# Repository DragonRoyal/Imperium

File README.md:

# Imperium
### An Autonomous, Sensor-Driven Chessboard with Electromagnetic Piece Control

## Abstract

**Imperium** is a fully autonomous chessboard that detects and moves pieces using a precision electromagnetic gantry, per-square Hall-effect sensing, and CNC-style motion control. The system integrates custom mechanical design, multi-PCB electronics, and firmware-level motion planning to deliver seamless, repeatable gameplay without manual calibration.

---

## System Overview

```mermaid
flowchart LR
    Pieces[Chess Pieces — Magnets]
    Sensors[Hall Sensor Matrix — 64 Squares]
    Mux[16:1 Multiplexers]
    MCU[ESP32 Master Controller]
    Drivers[TMC2209 Motor Drivers]
    Motors[Stepper Motors — T-Bot Gantry]
    Magnet[Electromagnet]

    Pieces --> Sensors
    Sensors --> Mux
    Mux --> MCU
    MCU --> Drivers
    Drivers --> Motors
    MCU --> Magnet
```

## Project Media

### Completed System

<p align="center">
  <em>Figure 2: Fully assembled Imperium chessboard</em>
</p>

### Videos
- 🎥 [demonstration video](https://www.youtube.com/watch?v=dJfiPbZPBKA)
- 🎥 [piece movement](https://www.youtube.com/watch?v=BL-nZTy-D_8)

---

## Hardware Architecture

### Mechanical Subsystem

<p align="center">
  <em>CAD Figure: T-Bot gantry layout and belt routing</em>
</p>

**Gantry Design**
- Type: **T-Bot (CoreXY derivative)**
- Motors: 2× NEMA 17
- Linear motion: 2× MGN12 rails (450 mm)
- Drive: GT2 belts & pulleys
- End effector: Electromagnet (custom mount)

**Design Rationale**
- Compact footprint compared to CoreXY  
- Sufficient precision for chess (no micron-level requirement)  
- Reduced part count and cost  

---

## Sensing Architecture

### Hall Sensor Matrix
```mermaid
flowchart LR
    Square1[Square 1]
    Square2[Square 2]
    SquareN[Square 64]
    Mux1[16:1 MUX]
    MCU[ESP32]

    Square1 --> Mux1
    Square2 --> Mux1
    SquareN --> Mux1
    Mux1 --> MCU
```

<p align="center">
  <em>Figure 5: 64-square Hall-effect sensor grid</em>
</p>

- Sensors: **KTH-1601 (46 Gs threshold)**
- 1 sensor per square (64 total)
- Mounted beneath ~3 mm acrylic

**Why Hall Sensors**
- Instantaneous response  
- No ghosting (unlike reed switches)  
- Reliable removal detection  

---

### PCB Sheet Layout
```mermaid
flowchart TB
    PCB1[Hall PCB Sheet 1\n16 Sensors]
    PCB2[Hall PCB Sheet 2\n16 Sensors]
    PCB3[Hall PCB Sheet 3\n16 Sensors]
    PCB4[Hall PCB Sheet 4\n16 Sensors]
    Master[Master PCB]

    PCB1 --> Master
    PCB2 --> Master
    PCB3 --> Master
    PCB4 --> Master
```

<p align="center">
  <em>Figure 6: Hall sensor PCB sheet (100 mm × 400 mm)</em>
</p>

Each PCB sheet contains:
- 16 Hall sensors  
- 1× 16:1 multiplexer  
- Local decoupling capacitors  
- Ribbon cable interface  

Total sheets: **4**

---

## Control Electronics

### Master Control Board

<p align="center">
  <em>Figure 7: Master PCB functional block diagram</em>
</p>

**Core Components**
- MCU: **ESP32**
- Motor drivers: **2× TMC2209 (UART)**
- Power:
  - 12 V rail (motors + electromagnet)
  - Buck converter → 3.3 V logic
- Electromagnet switching via transistor

All schematics and footprints were custom-designed in KiCad.

---

### UART Motor Control
Chess pieces are moved exclusively along square edges rather than diagonals. This design choice:

Prevents collisions with stationary pieces

Simplifies motion planning

Ensures consistent and predictable movement paths

The gantry executes all moves as a sequence of orthogonal segments.

UART enables:
- Sensorless homing  
- Stall detection  
- Current tuning  
- Advanced diagnostics  

---

### Control Flow

1. **Board State Detection**  
   Hall sensor matrix scans current piece positions.

2. **Move Translation**  
   Chess moves converted into constrained paths.

3. **G-Code Generation**  
   Custom G-code enforces non-diagonal movement.

4. **Execution**  
   G-code executed by **FluidNC** on ESP32.

---

## Bill of Materials (BOM)

📎 **Full BOM:**  
https://docs.google.com/spreadsheets/d/1yp7t6AiXMwJCAfVlhCX7udocGjks9lOOFWkv4rPJByo/view

---

## Results

- Reliable autonomous gameplay  
- Accurate per-square detection  
- Consistent homing and positioning  
- No recalibration required between games  

---

## Future Work

- Chess engine integration  
- Companion UI / mobile app  
- Faster traversal paths  
- Noise reduction  
- Fully enclosed consumer-ready housing  

---

## References

- CoreXY reference — https://corexy.com  
- Gantry design pitfalls — https://drmrehorst.blogspot.com  

---

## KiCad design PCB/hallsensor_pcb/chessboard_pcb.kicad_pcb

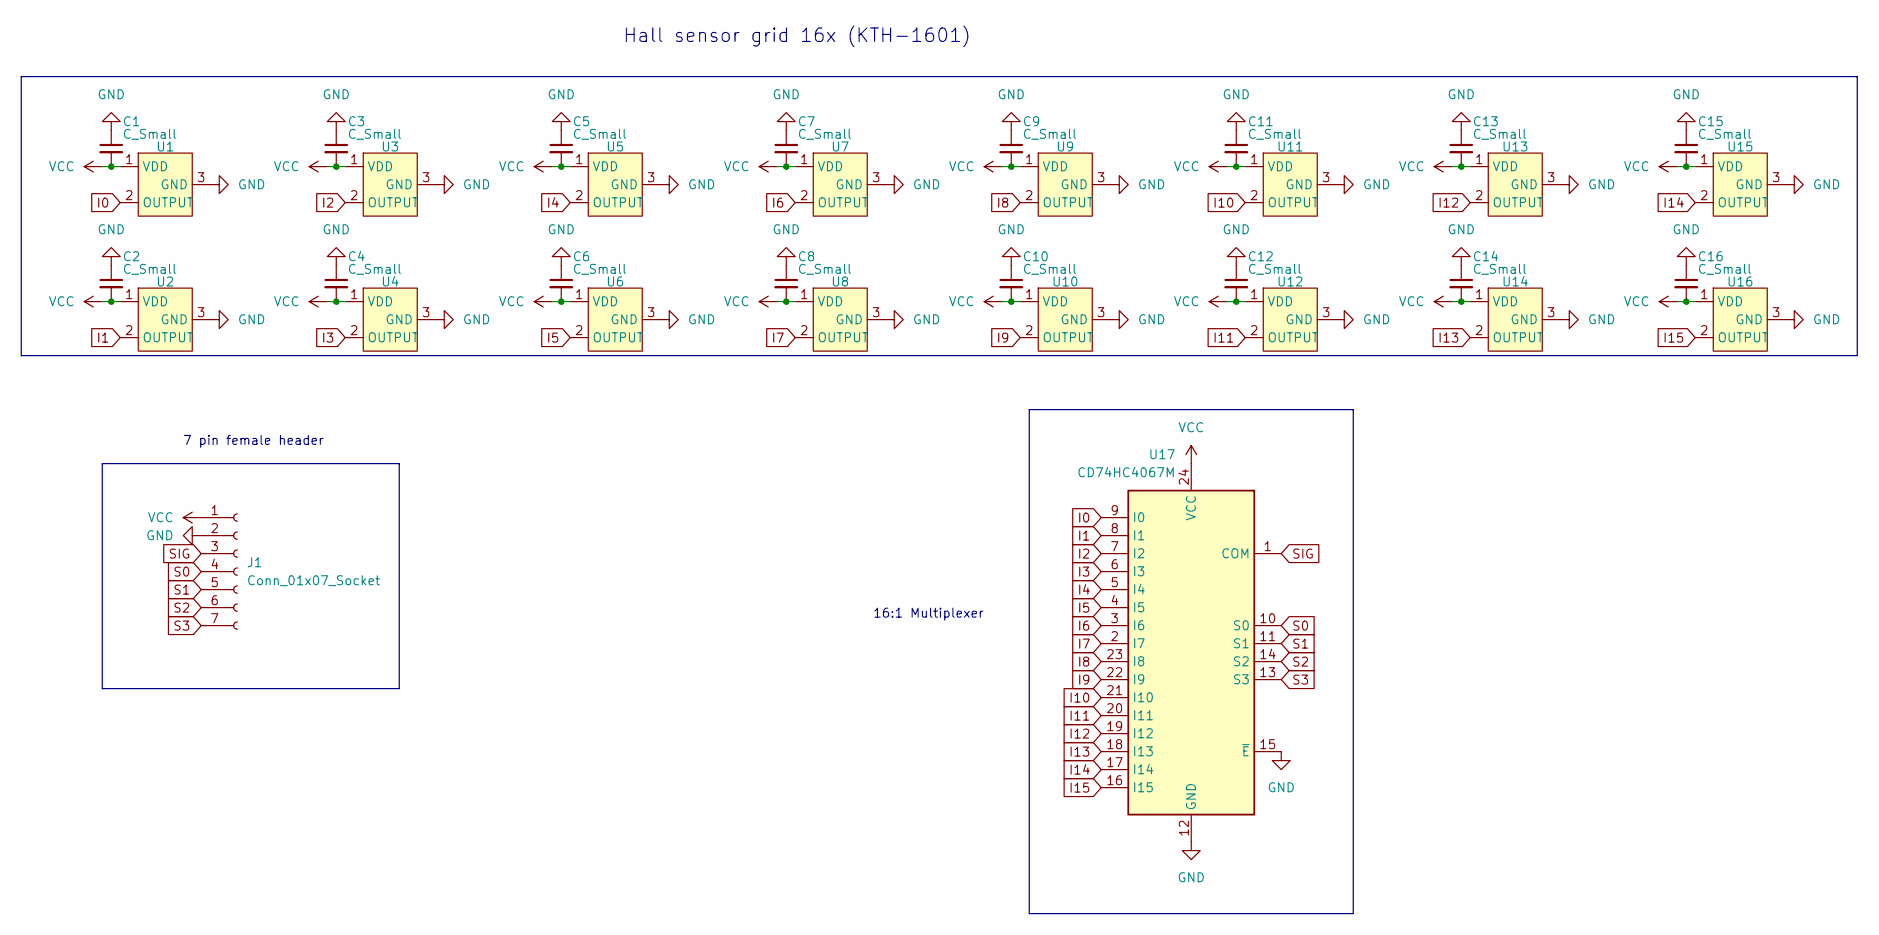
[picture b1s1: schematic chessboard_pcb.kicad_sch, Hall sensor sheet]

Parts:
C1, C2, C3, C4, C5, C6, C7, C8, C9, C10, C11, C12, C13, C14, C15, C16: C_Small; C_1206_3216Metric_Pad1.33x1.80mm_HandSolder
J1: Conn_01x07_Socket; IDC-Header_2x04_P2.54mm_Vertical
U1, U2, U3, U4, U5, U6, U7, U8, U9, U10, U11, U12, U13, U14, U15, U16: KTH_1601_S3
U17: CD74HC4067M; SOIC-24W_7.5x15.4mm_P1.27mm

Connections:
GND: C1.1, C2.1, C3.1, C4.1, C5.1, C6.1, C7.1, C8.1, C9.1, C10.1, C11.1, C12.1, C13.1, C14.1, C15.1, C16.1, J1.2, U1.3 (GND), U2.3 (GND), U3.3 (GND), U4.3 (GND), U5.3 (GND), U6.3 (GND), U7.3 (GND), U8.3 (GND), U9.3 (GND), U10.3 (GND), U11.3 (GND), U12.3 (GND), U13.3 (GND), U14.3 (GND), U15.3 (GND), U16.3 (GND), U17.12 (GND), U17.15 (~E)
I0: U1.2 (OUTPUT), U17.9 (I0)
I1: U2.2 (OUTPUT), U17.8 (I1)
I2: U3.2 (OUTPUT), U17.7 (I2)
I3: U4.2 (OUTPUT), U17.6 (I3)
I4: U5.2 (OUTPUT), U17.5 (I4)
I5: U6.2 (OUTPUT), U17.4 (I5)
I6: U7.2 (OUTPUT), U17.3 (I6)
I7: U8.2 (OUTPUT), U17.2 (I7)
I8: U9.2 (OUTPUT), U17.23 (I8)
I9: U10.2 (OUTPUT), U17.22 (I9)
I10: U11.2 (OUTPUT), U17.21 (I10)
I11: U12.2 (OUTPUT), U17.20 (I11)
I12: U13.2 (OUTPUT), U17.19 (I12)
I13: U14.2 (OUTPUT), U17.18 (I13)
I14: U15.2 (OUTPUT), U17.17 (I14)
I15: U16.2 (OUTPUT), U17.16 (I15)
S0: J1.4, U17.10 (S0)
S1: J1.5, U17.11 (S1)
S2: J1.6, U17.14 (S2)
S3: J1.7, U17.13 (S3)
SIG: J1.3, U17.1 (COM)
VCC: C1.2, C2.2, C3.2, C4.2, C5.2, C6.2, C7.2, C8.2, C9.2, C10.2, C11.2, C12.2, C13.2, C14.2, C15.2, C16.2, J1.1, U1.1 (VDD), U2.1 (VDD), U3.1 (VDD), U4.1 (VDD), U5.1 (VDD), U6.1 (VDD), U7.1 (VDD), U8.1 (VDD), U9.1 (VDD), U10.1 (VDD), U11.1 (VDD), U12.1 (VDD), U13.1 (VDD), U14.1 (VDD), U15.1 (VDD), U16.1 (VDD), U17.24 (VCC)

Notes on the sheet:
7 pin female header
16:1 Multiplexer
Hall sensor grid 16x (KTH-1601)

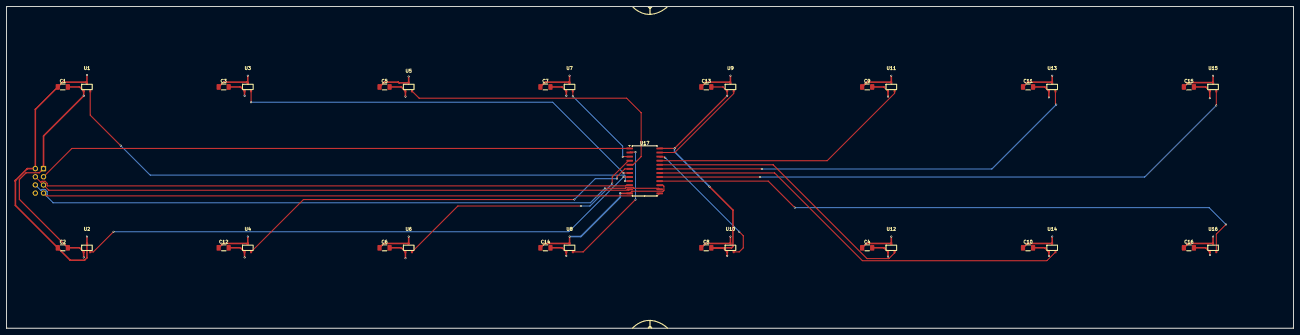
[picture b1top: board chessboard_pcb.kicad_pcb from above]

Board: 2 copper layers, 400.0 x 100.0 mm, 34 parts (1 on the bottom side), 23 nets.

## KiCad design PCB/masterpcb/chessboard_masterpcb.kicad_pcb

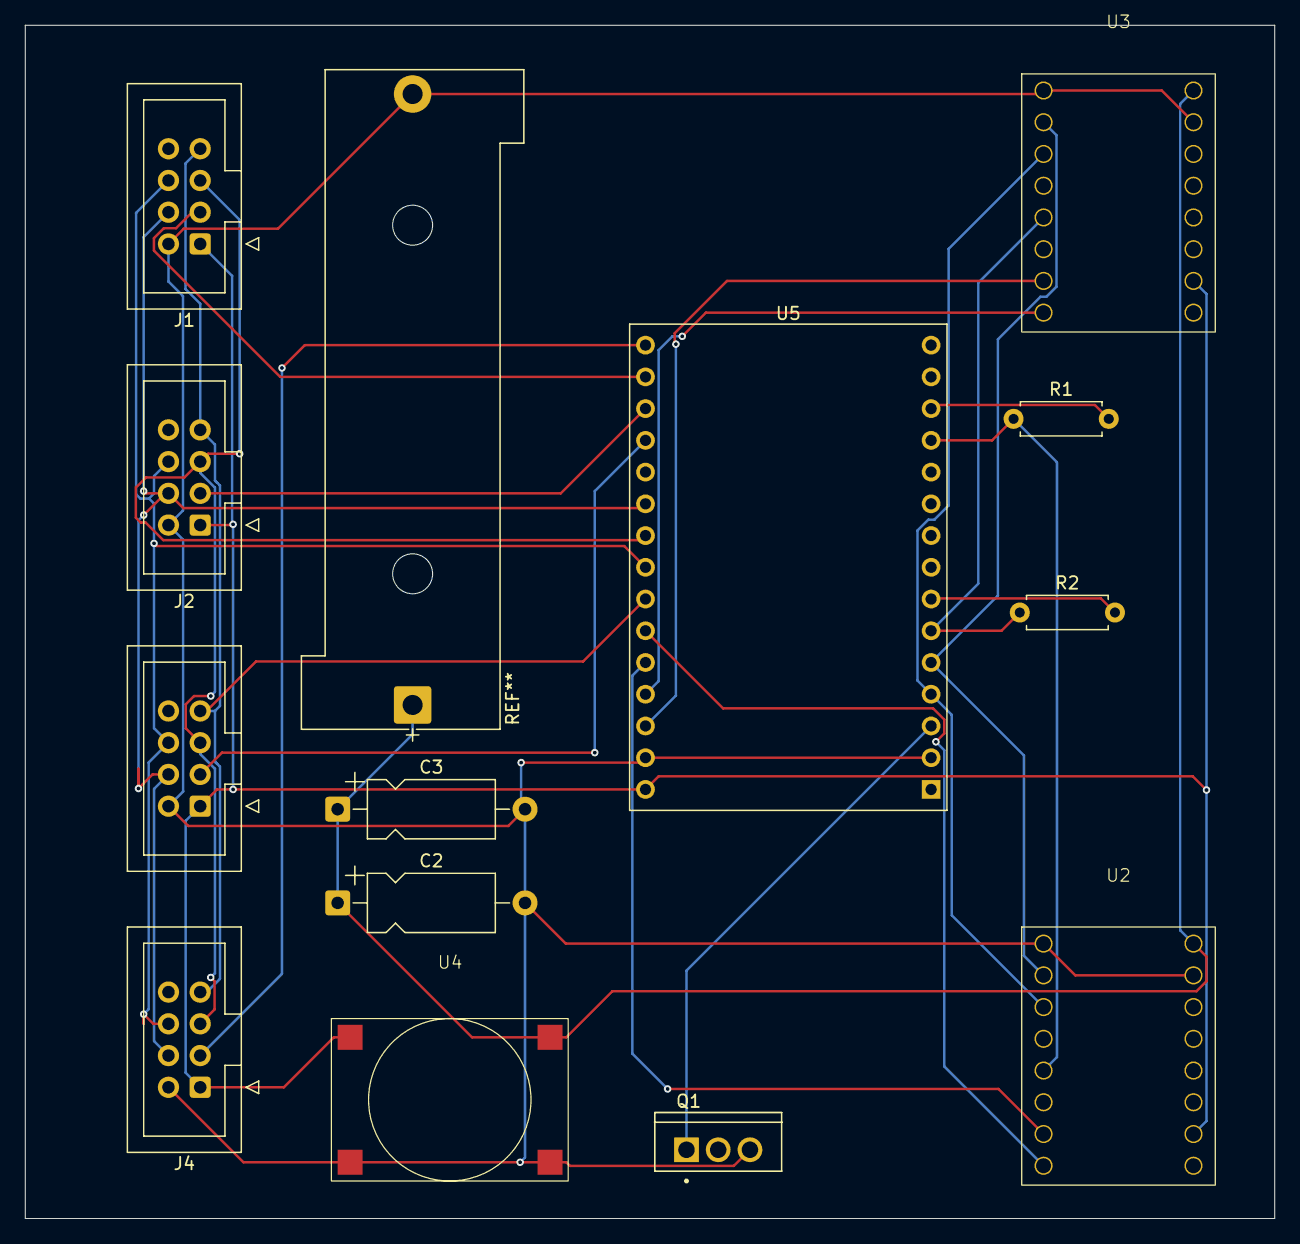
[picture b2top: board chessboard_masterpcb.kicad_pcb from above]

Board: 2 copper layers, 100.0 x 95.5 mm, 13 parts (0 on the bottom side), 22 nets.

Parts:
C2, C3: C_Small; CP_Axial_L10.0mm_D4.5mm_P15.00mm_Horizontal
J1, J2, J3, J4: Conn_01x07_Socket; IDC-Header_2x04_P2.54mm_Vertical
Q1: RFP30N06LE; TRANS_RFP30N06LE
R1, R2: R_Small; R_Axial_DIN0207_L6.3mm_D2.5mm_P7.62mm_Horizontal
U2, U3: TMC_2209 Big tree v1.3
U4: MP2303
U5: ESP32-C3-DevKitM-1

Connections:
DIR1: U3.8 (DIR), U5.19 (IO12)
DIR2: U2.8 (DIR), U5.21 (IO27)
GND: C2.2, C3.2, J1.2, J2.2, J3.2, J4.2, Q1.3, U2.1 (EN), U2.10 (GND), U3.1 (EN), U3.10 (GND), U4.2 (IN-), U4.4 (OUT-), U5.2 (GND), U5.17 (GND)
Gate: Q1.1, U5.3 (IO15)
MS1: U2.2 (MS1), U3.2 (MS1), U5.5 (IO4)
MS2: U2.3 (MS2), U3.3 (MS2), U5.4 (IO2)
unnamed: R1.2, U5.13 (TX0)
unnamed: R2.2, U5.7 (TX2)
S0: J1.4, J2.4, J3.4, J4.4, U5.25 (IO32)
S1: J1.5, J2.5, J3.5, J4.5, U5.24 (IO33)
S2: J1.6, J2.6, J3.6, J4.6, U5.23 (IO25)
S3: J1.7, J2.7, J3.7, J4.7, U5.22 (IO26)
SIG1: J4.3, U5.30 (EN)
SIG2: J1.3, U5.29 (IO36)
SIG3: J2.3, U5.28 (IO39)
SIG4: J3.3, U5.27 (IO34)
STEP1: U3.7 (STEP), U5.18 (IO13)
STEP2: U2.7 (STEP), U5.20 (IO14)
UART1: R1.1, U2.5 (USART), U5.12 (RX0)
UART2: R2.1, U3.5 (USART), U5.6 (RX2)
VDD: C2.1, C3.1, U2.9 (VM), U3.9 (VM), U4.1 (IN+)
VDD_3.3: J1.1, J2.1, J3.1, J4.1, U2.15 (VDD), U3.15 (VDD), U4.3 (OUT+), U5.16 (VIN)

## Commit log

2025-05-24 Rename Journal.md to JOURNAL.md
2025-06-14 Create txt6
2025-06-14 Create t
2026-01-02 Enhance README with project details and media
    Expanded the README to provide a detailed overview of the Imperium chessboard project, including its features, architecture, and media.
2026-01-02 Refine system overview diagram labels
    Updated descriptions in the system overview diagram for clarity.
2026-01-02 Revise CAD figure caption in README
    Updated the caption for the CAD figure in the README.
2026-01-02 Delete Electromagnet Assembly details from README
    Removed the Electromagnet Assembly section from the README.
